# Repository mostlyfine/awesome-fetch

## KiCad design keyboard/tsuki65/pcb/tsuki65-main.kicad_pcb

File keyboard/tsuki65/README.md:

# tsuki65

[torabo-tsuki LP](https://github.com/sekigon-gonnoc/torabo-tsuki-lp)（Mサイズ）をベースにした、自分用の
**ロウスタッガード（ANSI 風）4 行・数字列なしの分割キーボード + 14mm トラックボール** です。
左右の内側の辺はキーの境界ぴったりで切ってあるので、**くっつけると普通の一体型キーボード**として使えます。
マイコン（BMP Boost）と電源スイッチはロウスタッガードで生じる **外側の隙間** に置き、電池は底面に貼り付けます。

| 項目 | 仕様 |
| --- | --- |
| 形状 | 左右分割（合体可）、ロウスタッガード（行オフセット 0.5 / 0.75 / 1.25 U、全キー 1U、**数字列なしの 4 行**）。T｜Y・G｜H・B｜N・Spc｜Spc で分割 |
| キー数 | 52 キー（左 24 / 右 28、右下に矢印キー）+ 14mm トラックボール（マトリクス外）。数字・Esc・F キーはレイヤー |
| キーピッチ | **17 mm × 17 mm** |
| スイッチ | Kailh Choc V2（ホットスワップソケット CPG135001S30） |
| トラックボール | 14 mm、[maghold-trackball-case 14mm_17x17](https://github.com/shizu0428/maghold-trackball-case/tree/main/14mm-case_17x17) を **右手スペースの右隣（最下段）の 14×14 mm 穴に装着**（右親指で操作） |
| センサー | のぎけす屋 14mm マウスセンサーモジュール（PAW3222）、0.5 mm ピッチ 6P FPC |
| コントローラ | BMP Boost ×2（ピンアサインは torabo-tsuki LP と同一）。左: Ctrl/Shift の左の隙間、右: ]/Enter の右の隙間（どちらも USB は奥側の辺） |
| 電源 | 単三電池 ×1 / 片手（Ni-MH 可）、リード線付き電池ボックスをボトムプレート裏に貼り付け。スライドスイッチは外側の側面 |
| ファームウェア | ZMK（右手 = セントラル、左手 = ペリフェラル） |
| 基板サイズ | 左 約 131 × 81 mm / 右 約 157 × 81 mm、合体時 約 267 × 81 mm（スペーサー用の小さな耳を含む） |
| 構成 | メイン基板(1.6mm) / トッププレート(FR4 1.2mm) / ボトムプレート(FR4 1.6mm) / M2 4.5mm スペーサー |

torabo-tsuki LP M から引き継いでいるもの:

* マトリクス（ROW0-4 / COL0-6、row2col）と BMP Boost のピンアサイン、FPC コネクタの配線。
  → torabo-tsuki LP の ZMK 設定をほぼそのまま流用（`firmware/`）。
* プレート間を M2 × 4.5mm スペーサーで挟む積層構造（メイン基板には 5mm 穴）。

---

## ディレクトリ

```
keyboard/tsuki65/
├── fab/                      ← JLCPCB にそのままアップロードするファイル
│   ├── main/tsuki65-main-gerbers.zip       メイン基板（左右 + 外枠をマウスバイトで面付け）
│   ├── main/tsuki65-main-bom.csv           JLCPCB PCBA 用 BOM（LCSC 品番入り）
│   ├── main/tsuki65-main-cpl.csv           JLCPCB PCBA 用 部品配置ファイル（全部品 Bottom 面）
│   ├── top-plate/tsuki65-top-plate-gerbers.zip
│   └── bottom-plate/tsuki65-bottom-plate-gerbers.zip
├── pcb/                      ← KiCad 7 で開けるボードデータ（.kicad_pcb）とフットプリント
├── firmware/                 ← ZMK モジュール（そのまま zmk-config リポジトリとして使える）
├── img/                      ← プレビュー画像
└── scripts/                  ← 設計を全部生成するスクリプト（レイアウト変更→再生成できる）
```

| メイン基板（配線） | メイン基板（部品・裏面） |
| --- | --- |
|  |  |
| **トッププレート** | **ボトムプレート** |
|  |  |

---

## 1. JLCPCB に発注する

### 1-1. メイン基板（PCBA あり）

1. <https://cart.jlcpcb.com/quote> で `fab/main/tsuki65-main-gerbers.zip` をアップロード。
2. 基板設定
   * Base Material: FR-4 / Layers: **2** / PCB Thickness: **1.6 mm**
   * Dimensions: 自動（約 171 × 172 mm）
   * Different Design: **1**（左右と外枠はマウスバイトでつながった 1 枚のデータです。JLC から問い合わせが来たら「1 design (panel with mouse bites), please produce as is」と回答）
   * Mark on PCB（注文番号）: 「Remove Mark」推奨（無料オプションが無い場合は Order Number で可）
3. **PCB Assembly** をオン
   * PCBA Type: Economic / **Assembly Side: Bottom Side** / PCBA Qty: 2 以上
4. `fab/main/tsuki65-main-bom.csv` と `fab/main/tsuki65-main-cpl.csv` をアップロード。
5. 部品確認画面で以下を確認

   | 部品 | 数 | LCSC | 備考 |
   | --- | --- | --- | --- |
   | Kailh CPG135001S30（Choc ホットスワップソケット） | 52 | C5333465 | 在庫切れの場合は JLC 部品検索で `CPG135001S30` を探して差し替え。無ければ手はんだ（フットプリントは手はんだ用の大きめパッド） |
   | 1N4148W（SOD-123） | 52 | C81598 | Basic part |
   | GT-F0501SR10-06S1101（0.5mm 6P FPC コネクタ） | 1 | C22380676 | トラックボールセンサー用 |
   | K3-1280S-F1（スライドスイッチ） | 2 | C92658 | 電源スイッチ |
   | LED 0603 赤 | 2 | C2286 | 状態 LED |
   | 抵抗 1kΩ 0402 | 2 | C11702 | LED 用 |

6. **部品配置プレビューで向きを必ず確認**。特にダイオードの向き（カソード側＝ソケットに近い側）、
   ソケット、FPC コネクタ、スライドスイッチ（レバーが基板の外側の辺を向く）。
   各行の一番左のキーはソケットを 180° 回転して配置しています（合体する辺／マイコンにパッドがはみ出さないため）。

### 1-2. トッププレート

* `fab/top-plate/tsuki65-top-plate-gerbers.zip`、Layers: 2、**PCB Thickness: 1.2 mm**（Choc のプレート厚）
* 銅箔はありません。色はお好みで。スイッチ穴 13.8 mm 角、トラックボール位置（右手 Y の内側）は 14.0 mm 角。

### 1-3. ボトムプレート

* `fab/bottom-plate/tsuki65-bottom-plate-gerbers.zip`、Layers: 2、**PCB Thickness: 1.6 mm**
* 電池ボックスのリード線を通す穴と、電源スイッチのレバー用の切り欠きがあります。

### 1-4. 3D プリント（JLC3DP など）

| 部品 | データ | 数 |
| --- | --- | --- |
| 14mm トラックボールケース | [shizu0428/maghold-trackball-case `14mm-case_17x17/14mm_maghold-TBcase_v1.stl`](https://github.com/shizu0428/maghold-trackball-case/tree/main/14mm-case_17x17)（CC BY-NC 4.0、個人利用可・同梱していません） | 1 |

JLC3DP の手順は [torabo-tsuki LP ビルドガイド](https://github.com/sekigon-gonnoc/torabo-tsuki-lp/blob/main/build-guide.md#3dプリント部品の製造jlc3dp利用) と同じです。

## 2. 別途購入する部品

| 部品 | 数 | 備考 |
| --- | --- | --- |
| BMP Boost | 2 | BOOTH / 遊舎工房。BLE Micro Pro（無印）は不可 |
| コンスルー 13 ピン（高さ 2.5mm） | 4 | |
| 単三電池ボックス（1 本用・**リード線付き**） | 2 | ボトムプレート裏に両面テープで貼る。奥側に貼ると傾斜（チルト）が付きます |
| 単三電池 | 2 | Ni-MH 推奨 |
| Kailh Choc V2 スイッチ | 52 | |
| キーキャップ | 52 | **17 mm ピッチなので 16.5 mm 角以下** のロープロ用（Choc V2 は MX 互換ステム）。一般的な 17.5×16.5 mm の Choc キャップは横方向で干渉します |
| 14mm トラックボール（磁性あり） | 1 | maghold ケースの README 参照 |
| 14mm マウスセンサーモジュール | 1 | のぎけす屋 BOOTH |
| ベアリング 4×1.5×2 mm、M1.4 ねじ ×3、磁石 5×10×1 mm ×1 | 1 式 | maghold ケース用 |
| FFC 0.5mm ピッチ 6P（電極同一面）30〜50 mm 程度 | 1 | センサー⇔基板 |
| M2 スペーサー 4.5 mm | 11 | 左 5 本 / 右 6 本 |
| M2 × 3.5 mm ねじ | 22 | |
| ゴム足 | 8 | 薄型 |

## 3. 組み立て

1. メイン基板・プレートのマウスバイト（タブ）を折って外枠を外し、やすりで整える。
2. 電池ボックスのリード線をボトムプレートの穴（シルク「battery wires」）に通し、
   メイン基板の電池パッド（BT101 / BT201、シルク `+` `-`、角パッドが +）にはんだ付け。
   電池ボックスはボトムプレートの裏に両面テープで固定（奥側に貼ると手前下がりの傾斜になります）。
3. コンスルーを差して BMP Boost を載せる（部品面が上）。
4. トッププレートにスイッチをはめ、メイン基板のホットスワップソケットに差し込む。
5. トップ⇔ボトムを M2 × 4.5mm スペーサーで固定（メイン基板の 5mm 穴をスペーサーが貫通）。
6. トラックボール（右手）
   * maghold ケースを組み立て（磁石・ベアリング・センサー）。
   * FFC をケースのセンサーに挿し、**トッププレートの 14mm 穴 → メイン基板のスイッチ中央穴** を通して、
     基板裏の FPC コネクタ（J201、穴のすぐ右上）へ挿す。ケースを 14 mm 穴に差し込む。
7. 一体型として使うときは左右をくっつけて置くだけです（連結金具はありません）。

## 4. ファームウェア（ZMK）

`firmware/` は単体の zmk-config リポジトリになっています。

1. GitHub に新しいリポジトリ（例: `zmk-config-tsuki65`）を作り、`firmware/` の **中身** をルートに置いて push。
2. Actions が自動でビルド → Artifacts から以下をダウンロード
   * `tsuki65_right_central.uf2` … 右手（トラックボール側、PC と接続）
   * `tsuki65_left_peripheral.uf2` … 左手
   * `settings_reset.uf2` … ペアリングをやり直すとき
3. BMP Boost をブートローダーモードにして uf2 を書き込む（手順は torabo-tsuki LP ビルドガイドと同じ）。
4. キーマップは `firmware/config/tsuki65.keymap`、または ZMK Studio（USB 接続）で変更。
   既定のレイヤー
   * Lower（左親指）: 上段が Esc 1 2 3 4 5 6 7 8 9 0 - =、H J K L が矢印、N / M / , が左・右・中クリック、Tab の下が `
   * Raise（右親指）: 上段が F1〜F12・PrintScreen、H〜L 列が Home / PgDn / PgUp / End
   * Fn（左下）: Bluetooth 切替・USB/BLE 切替・ブートローダー
   USB は左右とも奥側の辺から挿せます。

トラックボールの向きが逆・90° ずれている場合は `firmware/boards/shields/tsuki65/tsuki65_right.overlay` の
`INPUT_TRANSFORM_*` を変更してください（maghold ケース内のセンサー向きに依存）。

## 5. 設計を変更する

レイアウトは `scripts/layout.py` に集約しています（ピッチ・各行のキーと位置・行スタッガード量・トラックボール位置。スペーサー位置は自動配置）。

```sh
# Ubuntu 24.04: apt install kicad python3-shapely python3-matplotlib ; pip install cairosvg
cd keyboard/tsuki65/scripts
./build_all.sh      # 部品配置 → 自動配線 → プレート → DRC → ガーバー/BOM/CPL → ZMK → 画像
```

* `gen_main.py`  メイン基板（フットプリント配置・ネット・外形・面付け）
* `route.py`     自作の 2 層グリッド自動配線（A* + リップアップ）
* `gen_plates.py` トップ/ボトムプレート
* `drc.py`       KiCad DRC（電気的エラー/未接続 0 でなければ失敗）
* `export_fab.py` JLCPCB 用出力
* `gen_fw.py`    ZMK のマトリクス変換・物理レイアウト・キーマップ
* 回路図（.kicad_sch）は作っていません。ネットは `gen_main.py` 内で定義しています（torabo-tsuki LP と同じ回路）。

### 回路（片手分）

* キー: ROW → ダイオード(A→K) → ソケット → COL（ZMK `row2col`）
* BMP Boost: 1 GND, 2 VCC, 3 LED, 6 SCLK, 7 SDIO, 8 MOTION, 9 CS, 10 COL0, 11 COL2, 12 COL4, 13 COL6, 14 COL5,
  15 COL3, 16 COL1, 17 未使用, 18 ROW3, 19 ROW2, 20 ROW1, 21 ROW0, 23 BOOT, 24 GND, 26 +BATT
* FPC: 1 GND, 2 SCLK, 3 SDIO, 4 MOTION, 5 CS, 6 VCC
* 電源スイッチ: BAT− ⇔ GND（ON）/ BOOT（ON 側はテスターか LED 点灯で確認してください）
* 電池: リード線パッド（+ = BATT → BMP 26 番、− = BAT− → 電源スイッチ）
* COL0 = 外側（小指側）から順に割当。右手のマトリクス列は ZMK で +7 オフセット。トラックボールはマトリクスに含まれません。
* 左右は鏡像ではありません（ロウスタッガードなので両手とも下の行ほど右にずれる）。

## 6. 検証状況と注意点

**試作はしていません。** 以下は確認済み/未確認です。

確認済み

* KiCad 7 DRC: メイン基板・両プレートとも配線/クリアランス/穴/外形エラー 0、未接続 0
  （残りはシルクとライブラリリンクの警告のみ）。配線幅 0.25 mm、クリアランス 0.2 mm、ビア 0.6/0.3 mm（JLC 標準仕様内）。
* torabo-tsuki LP と同じフットプリント・ピンアサイン。
* 左右の内側の辺は各行のキー境界と一致（合体時に隙間・干渉なし。面付けのタブ跡だけヤスリで平らに）。

未確認（発注前・組立時に確認してください）

* JLC の部品在庫（特に Choc ソケット C5333465）と、CPL の回転（裏面実装のため JLC プレビューで要確認）。
* FPC コネクタの差込方向とケーブル長（コネクタは接点側が西＝列間を向いています）。
* BMP Boost の USB コネクタ位置（ピン 1 側＝上側にある前提で配置しています）。
* maghold 14mm ケースと隣接キーキャップのクリアランス（17mm ピッチ用ケースなので問題ない想定）。
* 全キー 1U。Tab / Ctrl / Shift の左の隙間には左手の BMP Boost・電源スイッチ・電池パッド、
  ] / Enter / Up の右の隙間には右手の BMP Boost・電源スイッチ・電池パッドが入っています。
  torabo-tsuki LP の電池カバーはこの配置では使えません（BMP Boost は露出します）。
* ZMK ファームウェアはこの環境ではビルドしていません（torabo-tsuki LP の構成をベースにしています）。
* 17 mm ピッチではスイッチ間に 5 mm 穴を開ける余地がないため、スペーサーは外周
  （左 5 か所 / 右 6 か所、自動配置、合体する辺には置かない）に置き、外形に小さな耳を付けています。

## クレジット / ライセンス

* 基板フットプリント:
  [torabo-tsuki LP](https://github.com/sekigon-gonnoc/torabo-tsuki-lp) © sekigon-gonnoc, MIT License（`pcb/LICENSE-torabo-tsuki-lp`）
* ZMK 設定: [zmk-keyboard-torabo-tsuki-lp](https://github.com/sekigon-gonnoc/zmk-keyboard-torabo-tsuki-lp) ベース, GPL-3.0（`firmware/LICENSE`）
* 14mm トラックボールケース: [maghold-trackball-case](https://github.com/shizu0428/maghold-trackball-case) © shizu0428, CC BY-NC 4.0（同梱なし・リンクのみ）

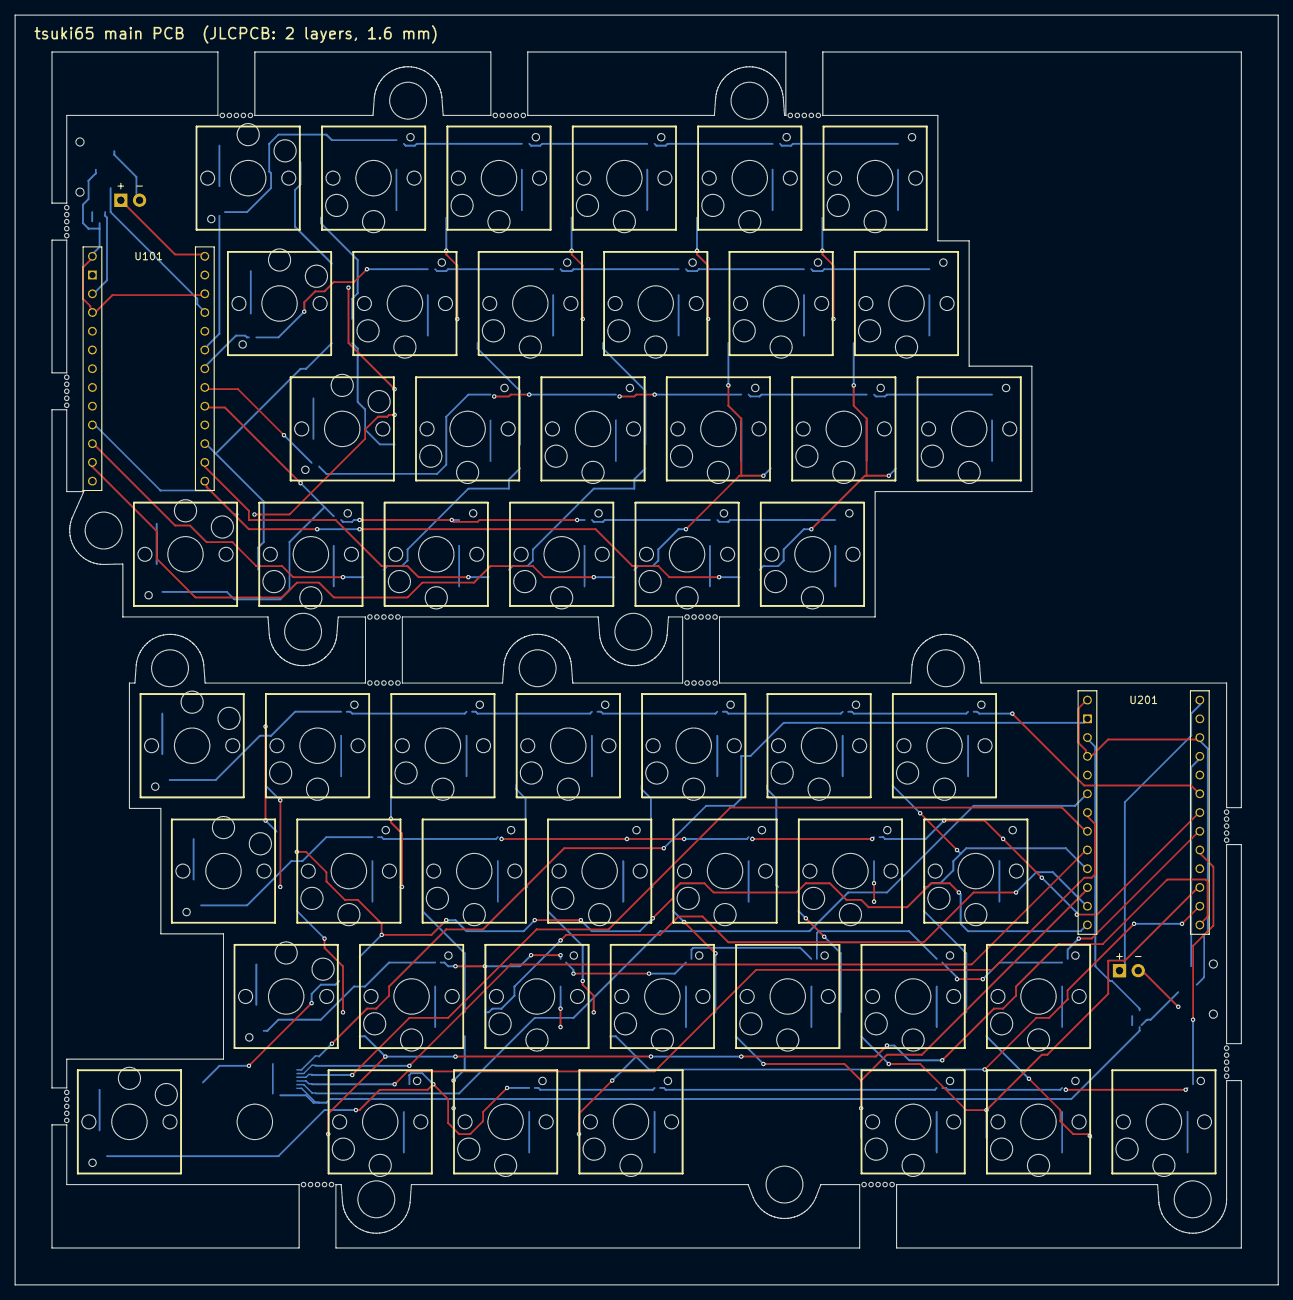
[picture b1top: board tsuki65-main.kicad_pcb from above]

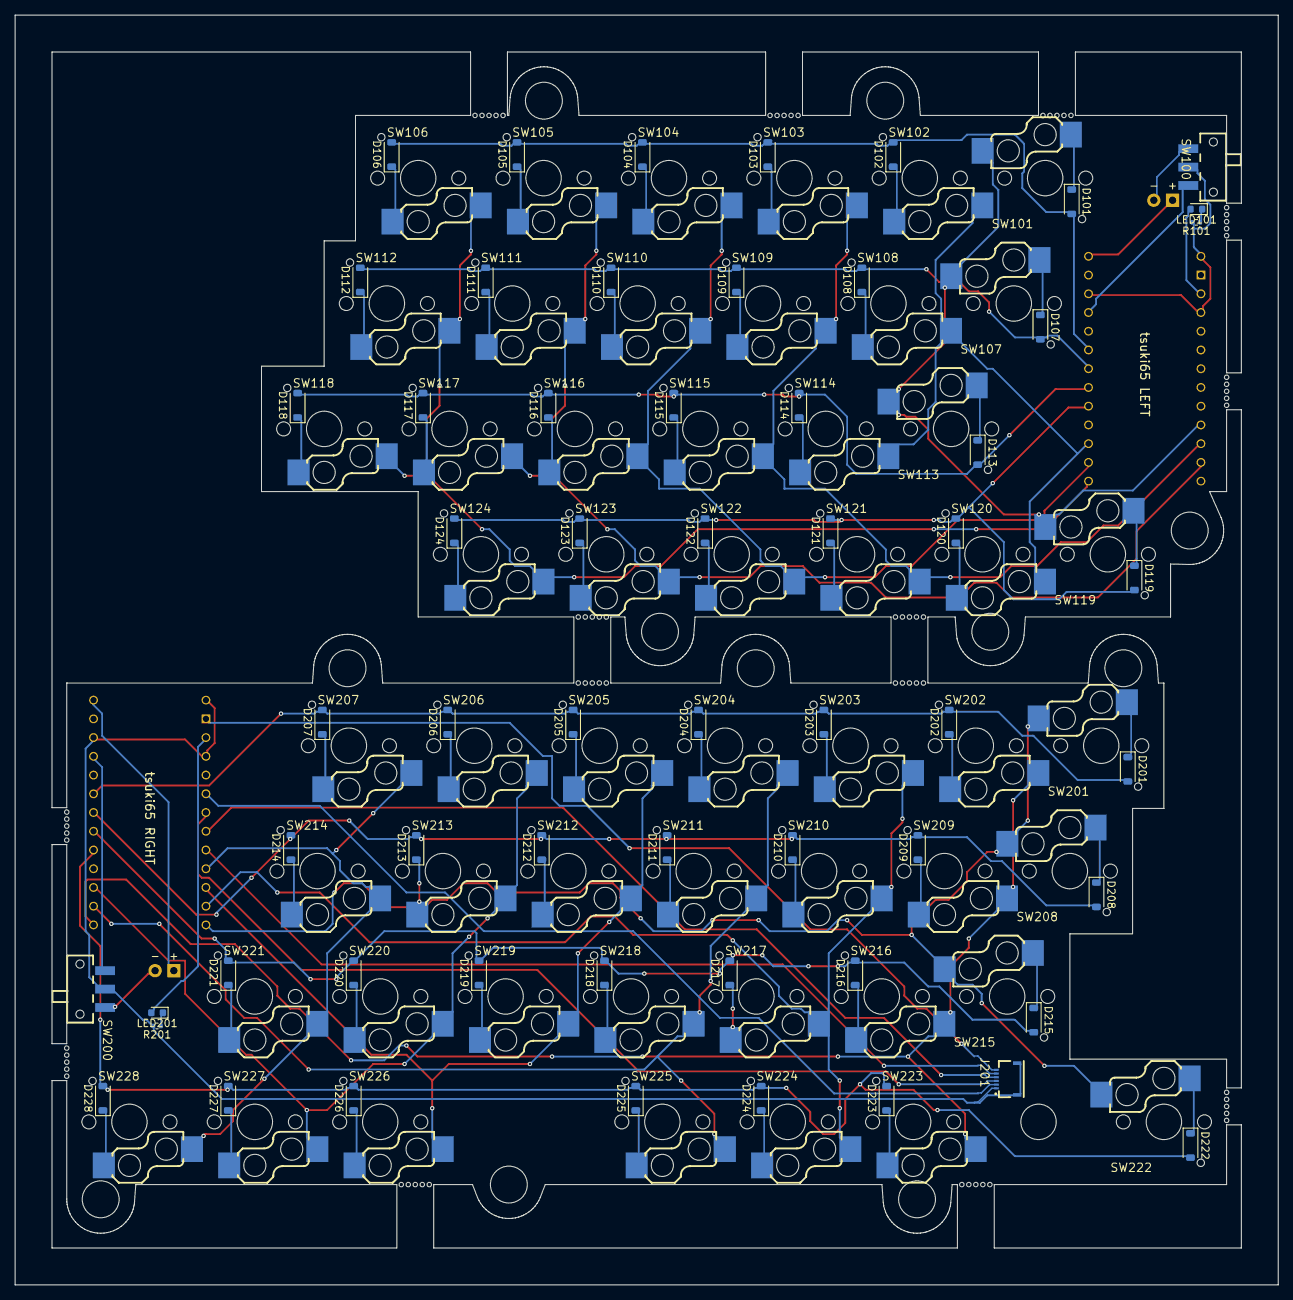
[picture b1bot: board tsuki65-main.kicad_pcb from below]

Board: 2 copper layers, 171.2 x 172.2 mm, 197 parts (111 on the bottom side), 90 nets.

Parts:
BT101, BT201: battery leads
D101, D102, D103, D104, D105, D106, D107, D108, D109, D110, D111, D112, D113, D114, D115, D116, D117, D118, D119, D120, D121, D122, D123, D124, D201, D202, D203, D204, D205, D206, D207, D208, D209, D210, D211, D212, D213, D214, D215, D216, D217, D218, D219, D220, D221, D222, D223, D224, D225, D226, D227, D228: 1N4148W; D_SOD-123
H160, H161, H162, H163, H164, H260, H261, H262, H263, H264, H265: MountingHole_5mm
HTBR: (no value)
J201: GT-F0501SR10-06S1101
LED101, LED201: LED red 0603; LED_0603_1608Metric
MB0, MB1, MB2, MB3, MB4, MB5, MB6, MB7, MB8, MB9, MB10, MB11, MB12, MB13, MB14, MB15, MB16, MB17, MB18, MB19, MB20, MB21, MB22, MB23, MB24, MB25, MB26, MB27, MB28, MB29, MB30, MB31, MB32, MB33, MB34, MB35, MB36, MB37, MB38, MB39, MB40, MB41, MB42, MB43, MB44, MB45, MB46, MB47, MB48, MB49, MB50, MB51, MB52, MB53, MB54, MB55, MB56, MB57, MB58, MB59, MB60, MB61, MB62, MB63, MB64, MB65, MB66, MB67, MB68, MB69: (no value)
R101, R201: 1k 0402; R_0402_1005Metric
SW100, SW200: K3-1280S-F1; SW-SMD_K3-1280S-F1
SW101, SW102, SW103, SW104, SW105, SW106, SW107, SW108, SW109, SW110, SW111, SW112, SW113, SW114, SW115, SW116, SW117, SW118, SW119, SW120, SW121, SW122, SW123, SW124, SW201, SW202, SW203, SW204, SW205, SW206, SW207, SW208, SW209, SW210, SW211, SW212, SW213, SW214, SW215, SW216, SW217, SW218, SW219, SW220, SW221, SW222, SW223, SW224, SW225, SW226, SW227, SW228: Kailh CPG135001S30; CHOC_V2_SOCKET_HANDSOLDERING
U101, U201: BMP Boost; BLEMicroPro

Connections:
L_BATN: BT101.2, SW100.1
L_BATT: BT101.1, U101.26
L_BOOT: SW100.3, U101.23
L_COL0: SW101.1, SW107.1, SW113.1, SW119.1, U101.10
L_COL1: SW102.1, SW108.1, SW114.1, SW120.1, U101.16
L_COL2: SW103.1, SW109.1, SW115.1, SW121.1, U101.11
L_COL3: SW104.1, SW110.1, SW116.1, SW122.1, U101.15
L_COL4: SW105.1, SW111.1, SW117.1, SW123.1, U101.12
L_COL5: SW106.1, SW112.1, SW118.1, SW124.1, U101.14
L_D101_K: D101.1, SW101.2
L_D102_K: D102.1, SW102.2
L_D103_K: D103.1, SW103.2
L_D104_K: D104.1, SW104.2
L_D105_K: D105.1, SW105.2
L_D106_K: D106.1, SW106.2
L_D107_K: D107.1, SW107.2
L_D108_K: D108.1, SW108.2
L_D109_K: D109.1, SW109.2
L_D110_K: D110.1, SW110.2
L_D111_K: D111.1, SW111.2
L_D112_K: D112.1, SW112.2
L_D113_K: D113.1, SW113.2
L_D114_K: D114.1, SW114.2
L_D115_K: D115.1, SW115.2
L_D116_K: D116.1, SW116.2
L_D117_K: D117.1, SW117.2
L_D118_K: D118.1, SW118.2
L_D119_K: D119.1, SW119.2
L_D120_K: D120.1, SW120.2
L_D121_K: D121.1, SW121.2
L_D122_K: D122.1, SW122.2
L_D123_K: D123.1, SW123.2
L_D124_K: D124.1, SW124.2
L_GND: R101.2, SW100.2, U101.1, U101.4, U101.24
L_LED: LED101.2, U101.3
L_LEDK: LED101.1, R101.1
L_ROW0: D101.2, D102.2, D103.2, D104.2, D105.2, D106.2, U101.21
L_ROW1: D107.2, D108.2, D109.2, D110.2, D111.2, D112.2, U101.20
L_ROW2: D113.2, D114.2, D115.2, D116.2, D117.2, D118.2, U101.19
L_ROW3: D119.2, D120.2, D121.2, D122.2, D123.2, D124.2, U101.18
R_BATN: BT201.2, SW200.1
R_BATT: BT201.1, U201.26
R_BOOT: SW200.3, U201.23
R_COL0: SW207.1, SW214.1, SW221.1, SW228.1, U201.10
R_COL1: SW206.1, SW213.1, SW220.1, SW227.1, U201.16
R_COL2: SW205.1, SW212.1, SW219.1, SW226.1, U201.11
R_COL3: SW204.1, SW211.1, SW218.1, SW225.1, U201.15
R_COL4: SW203.1, SW210.1, SW217.1, SW224.1, U201.12
R_COL5: SW202.1, SW209.1, SW216.1, SW223.1, U201.14
R_COL6: SW201.1, SW208.1, SW215.1, SW222.1, U201.13
R_CS: J201.5, U201.9
R_D201_K: D201.1, SW201.2
R_D202_K: D202.1, SW202.2
R_D203_K: D203.1, SW203.2
R_D204_K: D204.1, SW204.2
R_D205_K: D205.1, SW205.2
R_D206_K: D206.1, SW206.2
R_D207_K: D207.1, SW207.2
R_D208_K: D208.1, SW208.2
R_D209_K: D209.1, SW209.2
R_D210_K: D210.1, SW210.2
R_D211_K: D211.1, SW211.2
R_D212_K: D212.1, SW212.2
R_D213_K: D213.1, SW213.2
R_D214_K: D214.1, SW214.2
R_D215_K: D215.1, SW215.2
R_D216_K: D216.1, SW216.2
R_D217_K: D217.1, SW217.2
R_D218_K: D218.1, SW218.2
R_D219_K: D219.1, SW219.2
R_D220_K: D220.1, SW220.2
R_D221_K: D221.1, SW221.2
R_D222_K: D222.1, SW222.2
R_D223_K: D223.1, SW223.2
R_D224_K: D224.1, SW224.2
R_D225_K: D225.1, SW225.2
R_D226_K: D226.1, SW226.2
R_D227_K: D227.1, SW227.2
R_D228_K: D228.1, SW228.2
R_GND: J201.1, J201.MP, R201.2, SW200.2, U201.1, U201.4, U201.24
R_LED: LED201.2, U201.3
R_LEDK: LED201.1, R201.1
R_MOTION: J201.4, U201.8
R_ROW0: D201.2, D202.2, D203.2, D204.2, D205.2, D206.2, D207.2, U201.21
R_ROW1: D208.2, D209.2, D210.2, D211.2, D212.2, D213.2, D214.2, U201.20
R_ROW2: D215.2, D216.2, D217.2, D218.2, D219.2, D220.2, D221.2, U201.19
R_ROW3: D222.2, D223.2, D224.2, D225.2, D226.2, D227.2, D228.2, U201.18
R_SCLK: J201.2, U201.6
R_SDIO: J201.3, U201.7
R_VCC: J201.6, U201.2

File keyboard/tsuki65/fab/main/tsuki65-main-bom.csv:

Comment,Designator,Footprint,LCSC Part #
1N4148W,"D101,D102,D103,D104,D105,D106,D107,D108,D109,D110,D111,D112,D113,D114,D115,D116,D117,D118,D119,D120,D121,D122,D123,D124,D201,D202,D203,D204,D205,D206,D207,D208,D209,D210,D211,D212,D213,D214,D215,D216,D217,D218,D219,D220,D221,D222,D223,D224,D225,D226,D227,D228",D_SOD-123,C81598
1k 0402,"R101,R201",R_0402_1005Metric,C11702
GT-F0501SR10-06S1101,J201,GT-F0501SR10-06S1101,C22380676
K3-1280S-F1,"SW100,SW200",SW-SMD_K3-1280S-F1,C92658
Kailh CPG135001S30,"SW101,SW102,SW103,SW104,SW105,SW106,SW107,SW108,SW109,SW110,SW111,SW112,SW113,SW114,SW115,SW116,SW117,SW118,SW119,SW120,SW121,SW122,SW123,SW124,SW201,SW202,SW203,SW204,SW205,SW206,SW207,SW208,SW209,SW210,SW211,SW212,SW213,SW214,SW215,SW216,SW217,SW218,SW219,SW220,SW221,SW222,SW223,SW224,SW225,SW226,SW227,SW228",CHOC_V2_SOCKET_HANDSOLDERING,C5333465
LED red 0603,"LED101,LED201",LED_0603_1608Metric,C2286
